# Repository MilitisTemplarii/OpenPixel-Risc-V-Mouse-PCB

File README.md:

# OpenPixel-Risc-V-Mouse-PCB
Risc-V (CH32V305) based PCB for high-end gaming mouse

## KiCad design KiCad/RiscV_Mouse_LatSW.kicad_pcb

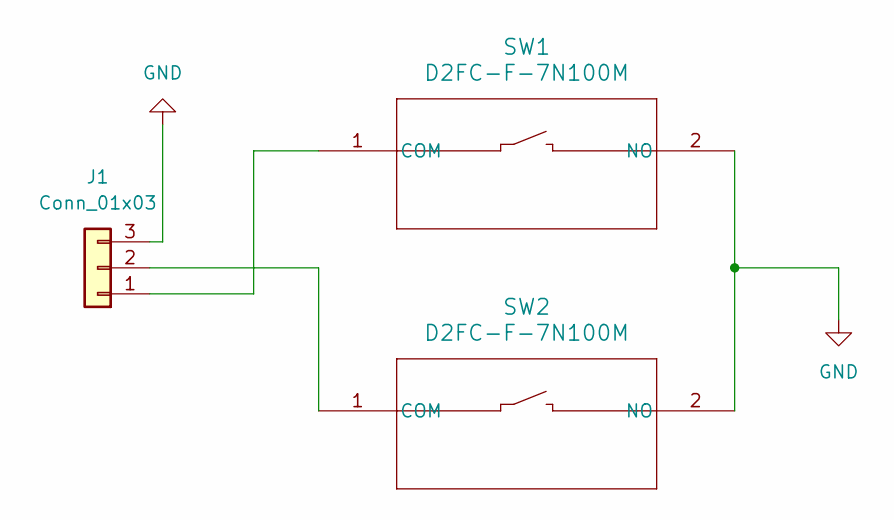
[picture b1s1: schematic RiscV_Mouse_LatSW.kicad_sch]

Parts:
J1: Conn_01x03; PinHeader_1x03_P1.00mm_Vertical
SW1, SW2: D2FC-F-7N100M; SW_D2FC_OMR

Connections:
GND: J1.3, SW1.2 (NO), SW2.2 (NO)
unnamed: J1.1, SW1.1 (COM)
unnamed: J1.2, SW2.1 (COM)

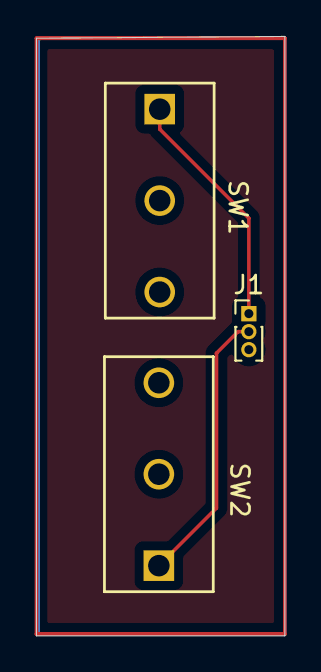
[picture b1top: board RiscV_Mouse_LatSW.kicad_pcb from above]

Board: 2 copper layers, 13.8 x 33.3 mm, 3 parts (0 on the bottom side), 3 nets.

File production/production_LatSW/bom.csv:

Designator,Footprint,Quantity,Value,LCSC Part #
J1,PinHeader_1x03_P1.00mm_Vertical,1,Conn_01x03,
"SW1, SW2",SW_D2FC_OMR,2,D2FC-F-7N100M,

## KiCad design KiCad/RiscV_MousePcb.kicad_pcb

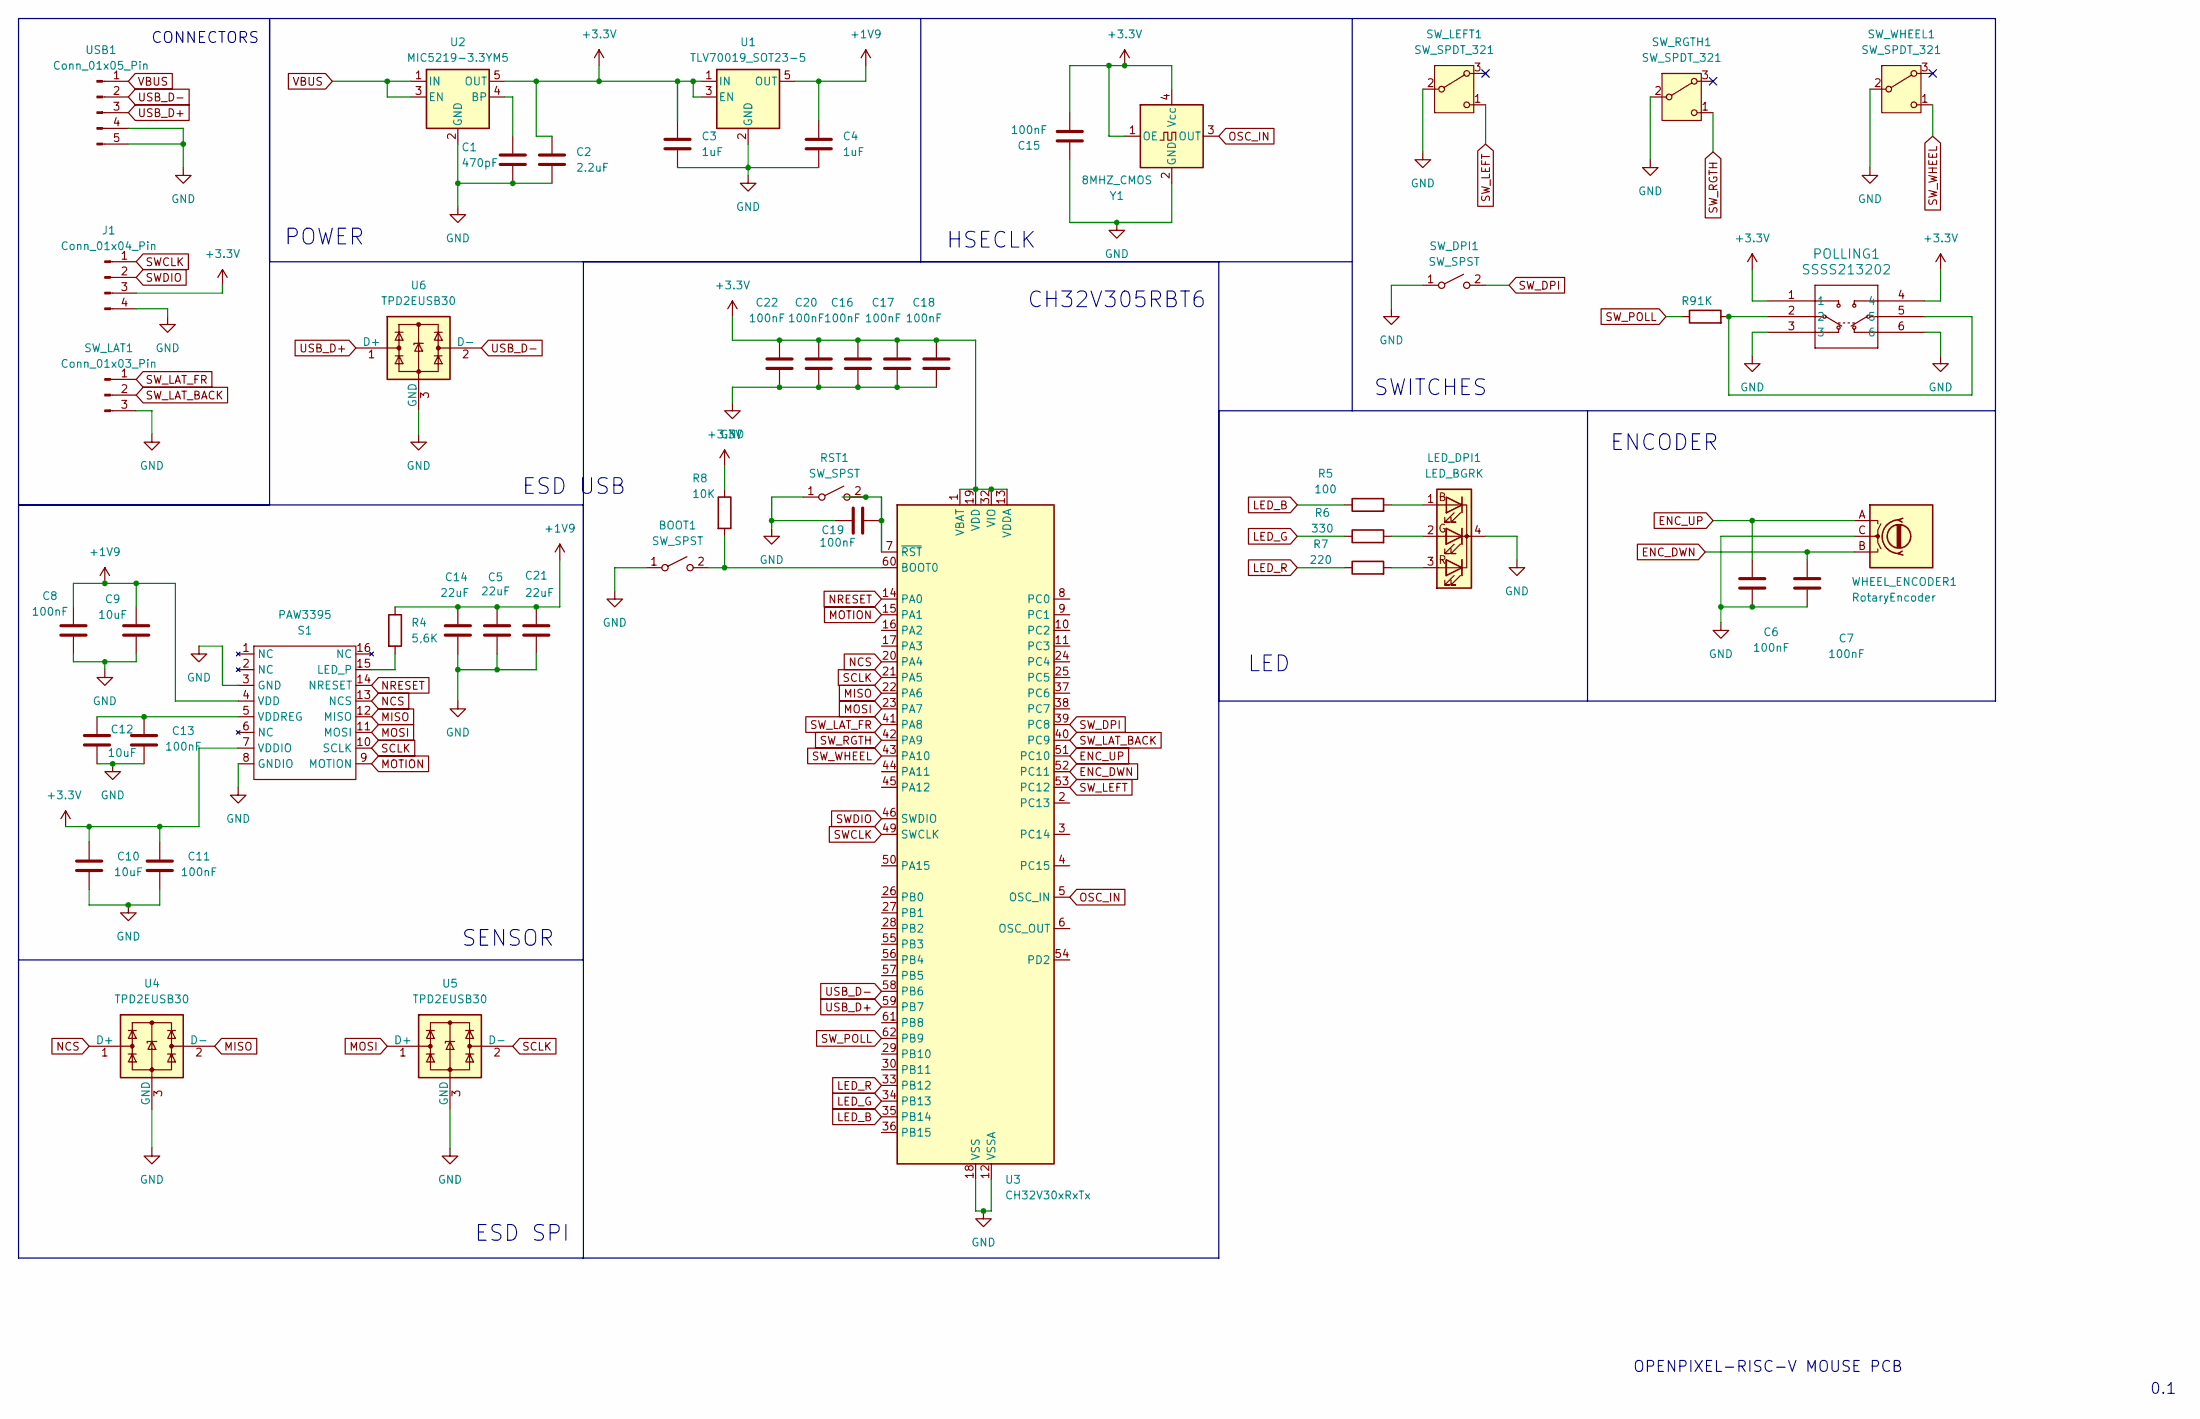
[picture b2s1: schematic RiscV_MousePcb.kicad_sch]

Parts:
BOOT1: SW_SPST; SW_SPST_TL3342
C1: 470pF; C_0805_2012Metric_Pad1.18x1.45mm_HandSolder
C2: 2.2uF; C_0805_2012Metric_Pad1.18x1.45mm_HandSolder
C3, C4: 1uF; C_0805_2012Metric_Pad1.18x1.45mm_HandSolder
C5, C14, C21: 22uF; C_0805_2012Metric_Pad1.18x1.45mm_HandSolder
C6, C7, C8, C11, C13, C15, C16, C17, C18, C19, C20, C22: 100nF; C_0805_2012Metric_Pad1.18x1.45mm_HandSolder
C9, C10, C12: 10uF; C_0805_2012Metric_Pad1.18x1.45mm_HandSolder
J1: Conn_01x04_Pin; PinHeader_1x04_P2.00mm_Vertical
LED_DPI1: LED_BGRK; LED_RGB_1210
PAW3395: S1; PAW3395_LGA16_fixed
POLLING1: SSSS213202; SSSS213202_AAL
R4: 5,6K; R_0805_2012Metric_Pad1.20x1.40mm_HandSolder
R5: 100; R_0805_2012Metric_Pad1.20x1.40mm_HandSolder
R6: 330; R_0805_2012Metric_Pad1.20x1.40mm_HandSolder
R7: 220; R_0805_2012Metric_Pad1.20x1.40mm_HandSolder
R8: 10K; R_0805_2012Metric_Pad1.20x1.40mm_HandSolder
R9: 1K; R_0805_2012Metric_Pad1.20x1.40mm_HandSolder
RST1: SW_SPST; SW_SPST_EVQP7C
SW_DPI1: SW_SPST; SW_SPST_TL3342
SW_LAT1: Conn_01x03_Pin; JST_SH_SM03B-SRSS-TB_1x03-1MP_P1.00mm_Horizontal
SW_LEFT1: SW_SPDT_321; SW_D2FC_OMR
SW_RGTH1: SW_SPDT_321; SW_D2FC_OMR
SW_WHEEL1: SW_SPDT_321; SW_D2FC_OMR
U1: TLV70019_SOT23-5; SOT-23-5
U2: MIC5219-3.3YM5; SOT-23-5
U3: CH32V30xRxTx; LQFP-64_10x10mm_P0.5mm
U4, U5, U6: TPD2EUSB30; Texas_DRT-3
USB1: Conn_01x05_Pin; JST_PH_S5B-PH-K_1x05_P2.00mm_Horizontal
WHEEL_ENCODER1: RotaryEncoder; Encoder_Kailh_Wheel_3Pin
Y1: 8MHZ_CMOS; Oscillator_SMD_SeikoEpson_SG210-4Pin_2.5x2.0mm

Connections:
+1V9: C4.1, C5.2, C8.1, C9.1, C14.2, C21.2, PAW3395.4 (VDD), R4.1, U1.5 (OUT)
+3.3V: C2.1, C3.1, C10.2, C11.2, C15.2, C16.1, C17.1, C18.1, C20.1, C22.1, J1.3, PAW3395.7 (VDDIO), POLLING1.1, POLLING1.4, R8.1, U1.1 (IN), U1.3 (EN), U2.5 (OUT), U3.1 (VBAT), U3.13 (VDDA), U3.19 (VDD), U3.32 (VIO), U3.48 (VDD), U3.64 (VIO), Y1.1 (OE), Y1.4 (Vcc)
ENC_DWN: C7.2, U3.52 (PC11), WHEEL_ENCODER1.B
ENC_UP: C6.2, U3.51 (PC10), WHEEL_ENCODER1.A
GND: BOOT1.1 (A), C1.2, C2.2, C3.2, C4.2, C5.1, C6.1, C7.1, C8.2, C9.2, C10.1, C11.1, C12.1, C13.1, C14.1, C15.1, C16.2, C17.2, C18.2, C19.1, C20.2, C21.1, C22.2, J1.4, LED_DPI1.4 (K), PAW3395.3 (GND), PAW3395.8 (GNDIO), POLLING1.3, POLLING1.6, RST1.1 (A), SW_DPI1.1 (A), SW_LAT1.3, SW_LEFT1.2 (B), SW_RGTH1.2 (B), SW_WHEEL1.2 (B), U1.2 (GND), U2.2 (GND), U3.12 (VSSA), U3.18 (VSS), U3.31 (VSS), U3.47 (VSS), U3.63 (VSS), U4.3 (GND), U5.3 (GND), U6.3 (GND), USB1.4, USB1.5, WHEEL_ENCODER1.C, Y1.2 (GND)
LED_B: R5.1, U3.35 (PB14)
LED_G: R6.1, U3.34 (PB13)
LED_R: R7.1, U3.33 (PB12)
MISO: PAW3395.12 (MISO), U3.22 (PA6), U4.2 (D-)
MOSI: PAW3395.11 (MOSI), U3.23 (PA7), U5.1 (D+)
MOTION: PAW3395.9 (MOTION), U3.15 (PA1)
NCS: PAW3395.13 (NCS), U3.20 (PA4), U4.1 (D+)
NRESET: PAW3395.14 (NRESET), U3.14 (PA0)
unnamed: BOOT1.2 (B), R8.2, U3.60 (BOOT0)
unnamed: LED_DPI1.1 (BA), R5.2
unnamed: LED_DPI1.2 (GA), R6.2
unnamed: LED_DPI1.3 (RA), R7.2
unnamed: PAW3395.15 (LED_P), R4.2
unnamed: C12.2, C13.2, PAW3395.5 (VDDREG)
unnamed: POLLING1.2, POLLING1.5, R9.2
unnamed: C19.2, RST1.2 (B), U3.7 (~RST)
unnamed: C1.1, U2.4 (BP)
OSC_IN: U3.5 (OSC_IN), Y1.3 (OUT)
SCLK: PAW3395.10 (SCLK), U3.21 (PA5), U5.2 (D-)
SWCLK: J1.1, U3.49 (SWCLK)
SWDIO: J1.2, U3.46 (SWDIO)
SW_DPI: SW_DPI1.2 (B), U3.39 (PC8)
SW_LAT_BACK: SW_LAT1.2, U3.40 (PC9)
SW_LAT_FR: SW_LAT1.1, U3.41 (PA8)
SW_LEFT: SW_LEFT1.1 (C), U3.53 (PC12)
SW_POLL: R9.1, U3.62 (PB9)
SW_RGTH: SW_RGTH1.1 (C), U3.42 (PA9)
SW_WHEEL: SW_WHEEL1.1 (C), U3.43 (PA10)
USB_D+: U3.59 (PB7), U6.1 (D+), USB1.3
USB_D-: U3.58 (PB6), U6.2 (D-), USB1.2
VBUS: U2.1 (IN), U2.3 (EN), USB1.1

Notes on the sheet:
LED
OPENPIXEL-RISC-V MOUSE PCB
0.1
SENSOR
CH32V305RBT6
ESD SPI
POWER
ENCODER
HSECLK
SWITCHES
CONNECTORS
ESD USB

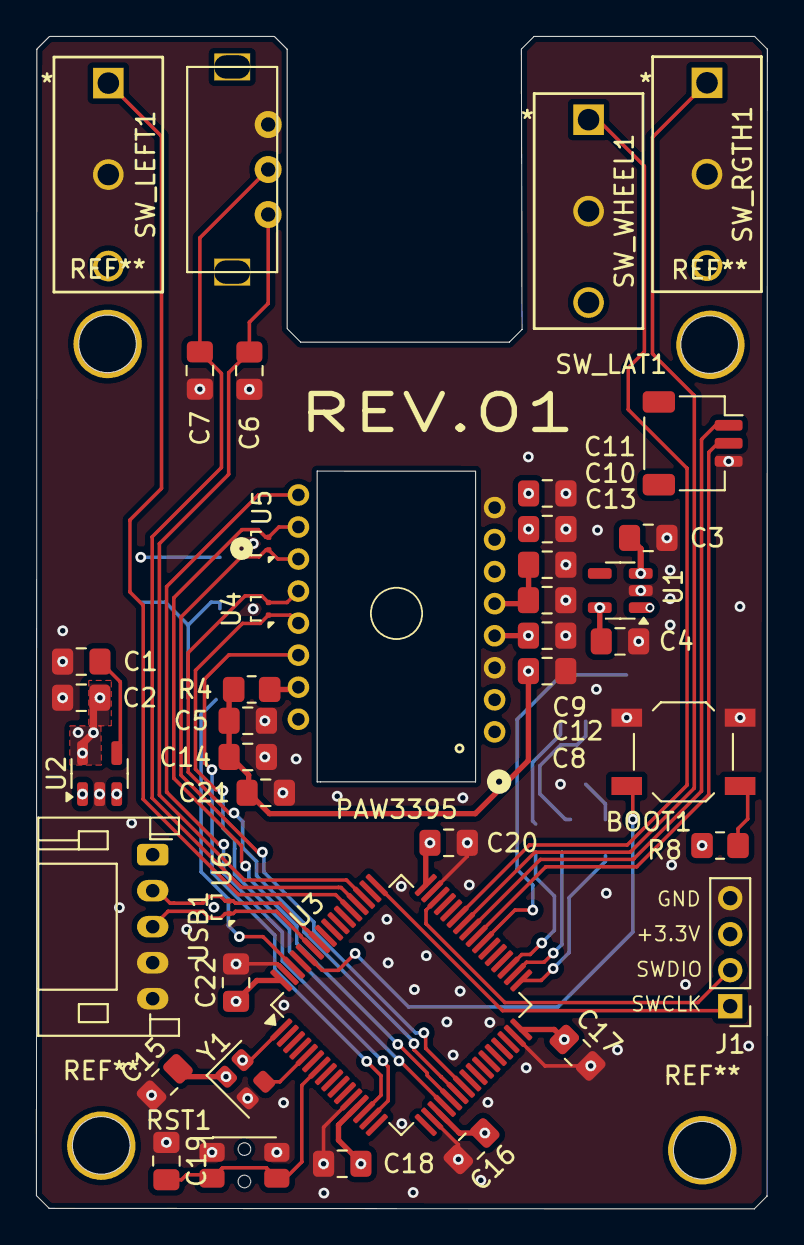
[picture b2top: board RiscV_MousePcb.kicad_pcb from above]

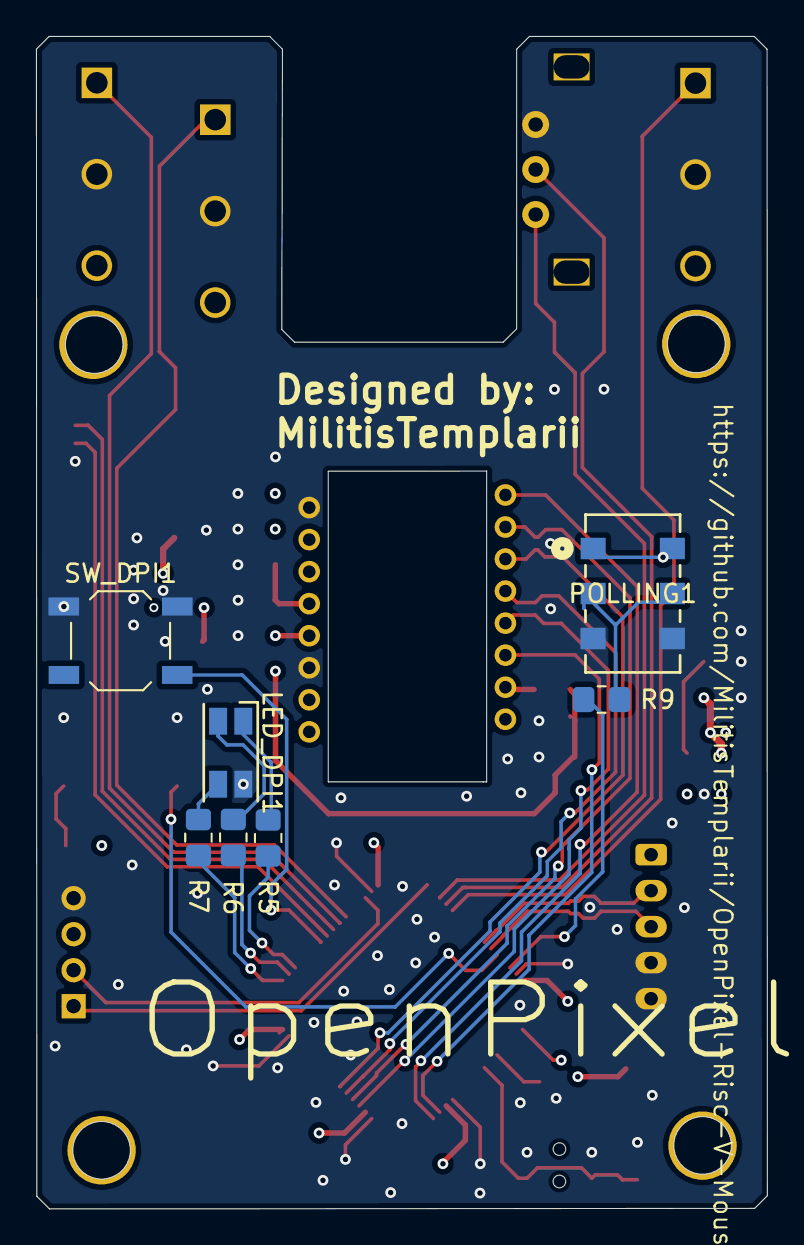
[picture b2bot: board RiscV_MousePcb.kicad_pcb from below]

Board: 4 copper layers, 40.6 x 65.1 mm, 48 parts (7 on the bottom side), 36 nets.

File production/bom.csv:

Designator,Footprint,Quantity,Value,LCSC Part #
"BOOT1, SW_DPI1",SW_SPST_TL3342,2,SW_SPST,
C1,0805,1,470pF,
"C10, C12, C9",0805,3,10uF,
"C11, C13, C15, C16, C17, C18, C19, C20, C22, C6, C7, C8",0805,12,100nF,
"C14, C21, C5",0805,3,22uF,
C2,0805,1,2.2uF,
"C3, C4",0805,2,1uF,
J1,PinHeader_1x04_P2.00mm_Vertical,1,Conn_01x04_Pin,
LED_DPI1,LED_RGB_1210,1,LED_BGRK,
PAW3395,PAW3395_LGA16_fixed,1,S1,
POLLING1,SSSS213202_AAL,1,SSSS213202,
R4,0805,1,"5,6K",
R5,0805,1,100,
R6,0805,1,330,
R7,0805,1,220,
R8,0805,1,10K,
R9,0805,1,1K,
RST1,SW_SPST_EVQP7C,1,SW_SPST,
SW_LAT1,JST_SH_SM03B-SRSS-TB_1x03-1MP_P1.00mm_Horizontal,1,Conn_01x03_Pin,
"SW_LEFT1, SW_RGTH1, SW_WHEEL1",SW_D2FC_OMR,3,SW_SPDT_321,
U1,SOT-23-5,1,TLV70019_SOT23-5,
U2,SOT-23-5,1,MIC5219-3.3YM5,
U3,LQFP-64_10x10mm_P0.5mm,1,CH32V30xRxTx,
"U4, U5, U6",Texas_DRT-3,3,TPD2EUSB30,
USB1,JST_PH_S5B-PH-K_1x05_P2.00mm_Horizontal,1,Conn_01x05_Pin,
WHEEL_ENCODER1,Encoder_Kailh_Wheel_3Pin,1,RotaryEncoder,
Y1,Oscillator_SMD_SeikoEpson_SG210-4Pin_2.5x2.0mm,1,8MHZ_CMOS,

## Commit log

2025-10-07 Add files via upload
    Added ESD protection to sensor SPI bus and USB tracks
2026-03-08 Add images to README for better visualization
    Added images to enhance the README with visual content.
2026-03-08 Clarify Risc-V model in README header
